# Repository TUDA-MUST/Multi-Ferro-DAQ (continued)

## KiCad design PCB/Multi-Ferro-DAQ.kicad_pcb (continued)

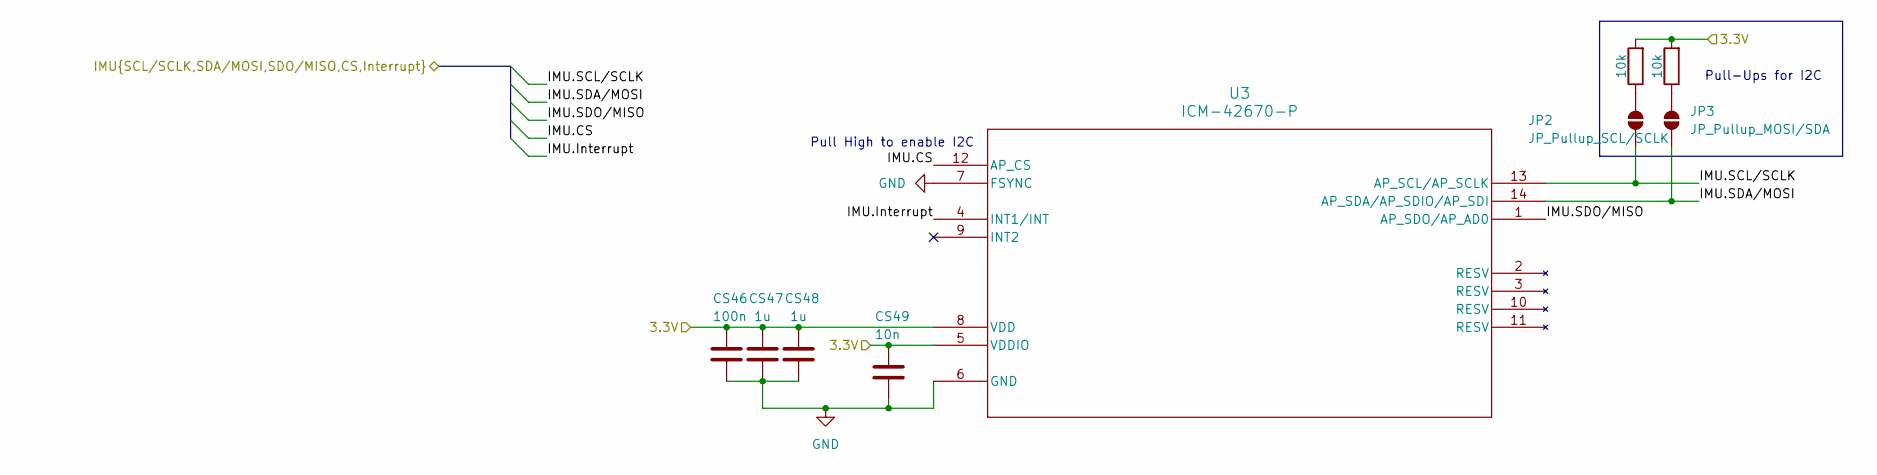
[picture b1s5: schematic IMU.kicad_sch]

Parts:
CS46: 100n; C_0603_1608Metric; LCSC C14663
CS47, CS48: 1u; C_0603_1608Metric; LCSC C15849
CS49: 10n; C_0603_1608Metric; LCSC C57112
JP2: JP_Pullup_SCL/SCLK; SolderJumper-2_P1.3mm_Open_RoundedPad1.0x1.5mm
JP3: JP_Pullup_MOSI/SDA; SolderJumper-2_P1.3mm_Open_RoundedPad1.0x1.5mm
R15, R16: 10k; R_0603_1608Metric; LCSC C25804
U3: ICM-42670-P; LGA14_2.5X3X0.76_IVS; LCSC C3288646

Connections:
/ADC/DVDD: CS46.2, CS47.1, CS48.1, CS49.2, R15.2, R16.2, U3.5 (VDDIO), U3.8 (VDD); also elsewhere on the board
/ESP32/IMU.CS: U3.12 (AP_CS); also elsewhere on the board
/ESP32/IMU.Interrupt: U3.4 (INT1/INT); also elsewhere on the board
/ESP32/IMU.SCL/SCLK: JP2.1 (A), U3.13 (AP_SCL/AP_SCLK); also elsewhere on the board
/ESP32/IMU.SDA/MOSI: JP3.1 (A), U3.14 (AP_SDA/AP_SDIO/AP_SDI); also elsewhere on the board
/ESP32/IMU.SDO/MISO: U3.1 (AP_SDO/AP_AD0); also elsewhere on the board
GND: CS46.1, CS47.2, CS48.2, CS49.1, U3.6 (GND), U3.7 (FSYNC); also elsewhere on the board
unnamed: JP2.2 (B), R15.1
unnamed: JP3.2 (B), R16.1

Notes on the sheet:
Pull-Ups for I2C
Pull High to enable I2C

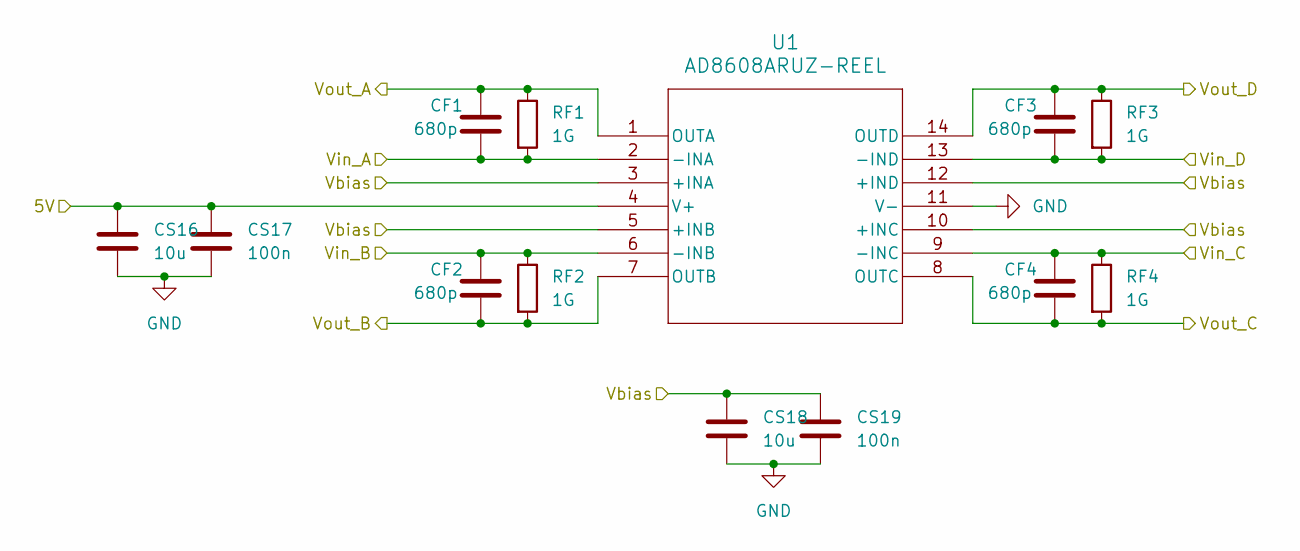
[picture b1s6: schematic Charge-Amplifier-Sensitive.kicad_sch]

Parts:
CF1, CF2, CF3, CF4: 680p; C_0805_2012Metric_Pad1.18x1.45mm_HandSolder; LCSC C1835
CS16, CS18: 10u; C_0603_1608Metric; LCSC C19702
CS17, CS19: 100n; C_0603_1608Metric; LCSC C14663
RF1, RF2, RF3, RF4: 1G; R_0805_2012Metric_Pad1.20x1.40mm_HandSolder; LCSC C2484710
U1: AD8608ARUZ-REEL; RU_14_ADI; LCSC C578777

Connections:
/ADC/AVDD: CS16.1, CS17.1, U1.4 (V+); also elsewhere on the board
/ADC/Charge-Amplifier-PORT I/Vin_A: CF1.2, RF1.2, U1.2 (-INA); also elsewhere on the board
/ADC/Charge-Amplifier-PORT I/Vin_B: CF2.1, RF2.1, U1.6 (-INB); also elsewhere on the board
/ADC/Charge-Amplifier-PORT I/Vin_C: CF4.1, RF4.1, U1.9 (-INC); also elsewhere on the board
/ADC/Charge-Amplifier-PORT I/Vin_D: CF3.2, RF3.2, U1.13 (-IND); also elsewhere on the board
/ADC/Charge-Amplifier-PORT I/Vout_A: CF1.1, RF1.1, U1.1 (OUTA); also elsewhere on the board
/ADC/Charge-Amplifier-PORT I/Vout_B: CF2.2, RF2.2, U1.7 (OUTB); also elsewhere on the board
/ADC/Charge-Amplifier-PORT I/Vout_C: CF4.2, RF4.2, U1.8 (OUTC); also elsewhere on the board
/ADC/Charge-Amplifier-PORT I/Vout_D: CF3.1, RF3.1, U1.14 (OUTD); also elsewhere on the board
/ADC/Vbias: CS18.1, CS19.1, U1.3 (+INA), U1.5 (+INB), U1.10 (+INC), U1.12 (+IND); also elsewhere on the board
GND: CS16.2, CS17.2, CS18.2, CS19.2, U1.11 (V-); also elsewhere on the board

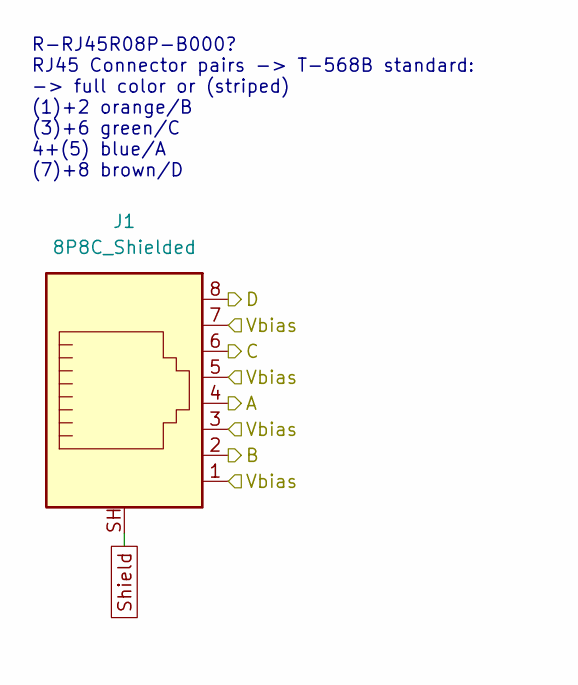
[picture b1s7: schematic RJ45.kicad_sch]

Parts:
J1: 8P8C_Shielded; R-RJ45R08P-B000; LCSC C386756

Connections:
/ADC/Charge-Amplifier-PORT I/Vin_A: J1.4; also elsewhere on the board
/ADC/Charge-Amplifier-PORT I/Vin_B: J1.2; also elsewhere on the board
/ADC/Charge-Amplifier-PORT I/Vin_C: J1.6; also elsewhere on the board
/ADC/Charge-Amplifier-PORT I/Vin_D: J1.8; also elsewhere on the board
/ADC/Vbias: J1.1, J1.3, J1.5, J1.7; also elsewhere on the board
Shield: J1.SH; also elsewhere on the board

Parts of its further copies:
J5: 8P8C_Shielded; R-RJ45R08P-B000; LCSC C386756

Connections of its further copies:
/ADC/Charge-Amplifier-PORT II/Vin_A: J5.4; also elsewhere on the board
/ADC/Charge-Amplifier-PORT II/Vin_B: J5.2; also elsewhere on the board
/ADC/Charge-Amplifier-PORT II/Vin_C: J5.6; also elsewhere on the board
/ADC/Charge-Amplifier-PORT II/Vin_D: J5.8; also elsewhere on the board
/ADC/Vbias: J5.1, J5.3, J5.5, J5.7; also elsewhere on the board
Shield: J5.SH; also elsewhere on the board

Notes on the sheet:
R-RJ45R08P-B000? RJ45 Connector pairs -> T-568B standard: -> full color or (striped) (1)+2 orange/B (3)+6 green/C 4+(5) blue/A (7)+8 brown/D

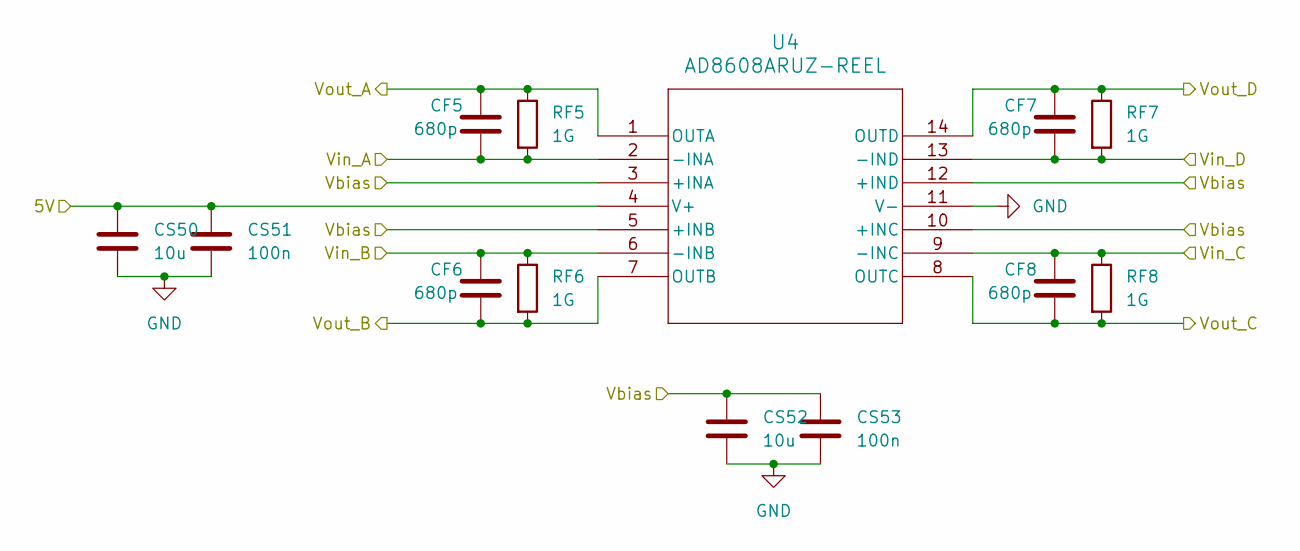
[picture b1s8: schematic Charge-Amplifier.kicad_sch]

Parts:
CF5, CF6, CF7, CF8: 680p; C_0805_2012Metric_Pad1.18x1.45mm_HandSolder; LCSC C1835
CS50, CS52: 10u; C_0603_1608Metric; LCSC C19702
CS51, CS53: 100n; C_0603_1608Metric; LCSC C14663
RF5, RF6, RF7, RF8: 1G; R_0805_2012Metric_Pad1.20x1.40mm_HandSolder; LCSC C2484710
U4: AD8608ARUZ-REEL; RU_14_ADI; LCSC C578777

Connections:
/ADC/AVDD: CS50.1, CS51.1, U4.4 (V+); also elsewhere on the board
/ADC/Charge-Amplifier-PORT II/Vin_A: CF5.2, RF5.2, U4.2 (-INA); also elsewhere on the board
/ADC/Charge-Amplifier-PORT II/Vin_B: CF6.1, RF6.1, U4.6 (-INB); also elsewhere on the board
/ADC/Charge-Amplifier-PORT II/Vin_C: CF8.1, RF8.1, U4.9 (-INC); also elsewhere on the board
/ADC/Charge-Amplifier-PORT II/Vin_D: CF7.2, RF7.2, U4.13 (-IND); also elsewhere on the board
/ADC/Charge-Amplifier-PORT II/Vout_A: CF5.1, RF5.1, U4.1 (OUTA); also elsewhere on the board
/ADC/Charge-Amplifier-PORT II/Vout_B: CF6.2, RF6.2, U4.7 (OUTB); also elsewhere on the board
/ADC/Charge-Amplifier-PORT II/Vout_C: CF8.2, RF8.2, U4.8 (OUTC); also elsewhere on the board
/ADC/Charge-Amplifier-PORT II/Vout_D: CF7.1, RF7.1, U4.14 (OUTD); also elsewhere on the board
/ADC/Vbias: CS52.1, CS53.1, U4.3 (+INA), U4.5 (+INB), U4.10 (+INC), U4.12 (+IND); also elsewhere on the board
GND: CS50.2, CS51.2, CS52.2, CS53.2, U4.11 (V-); also elsewhere on the board

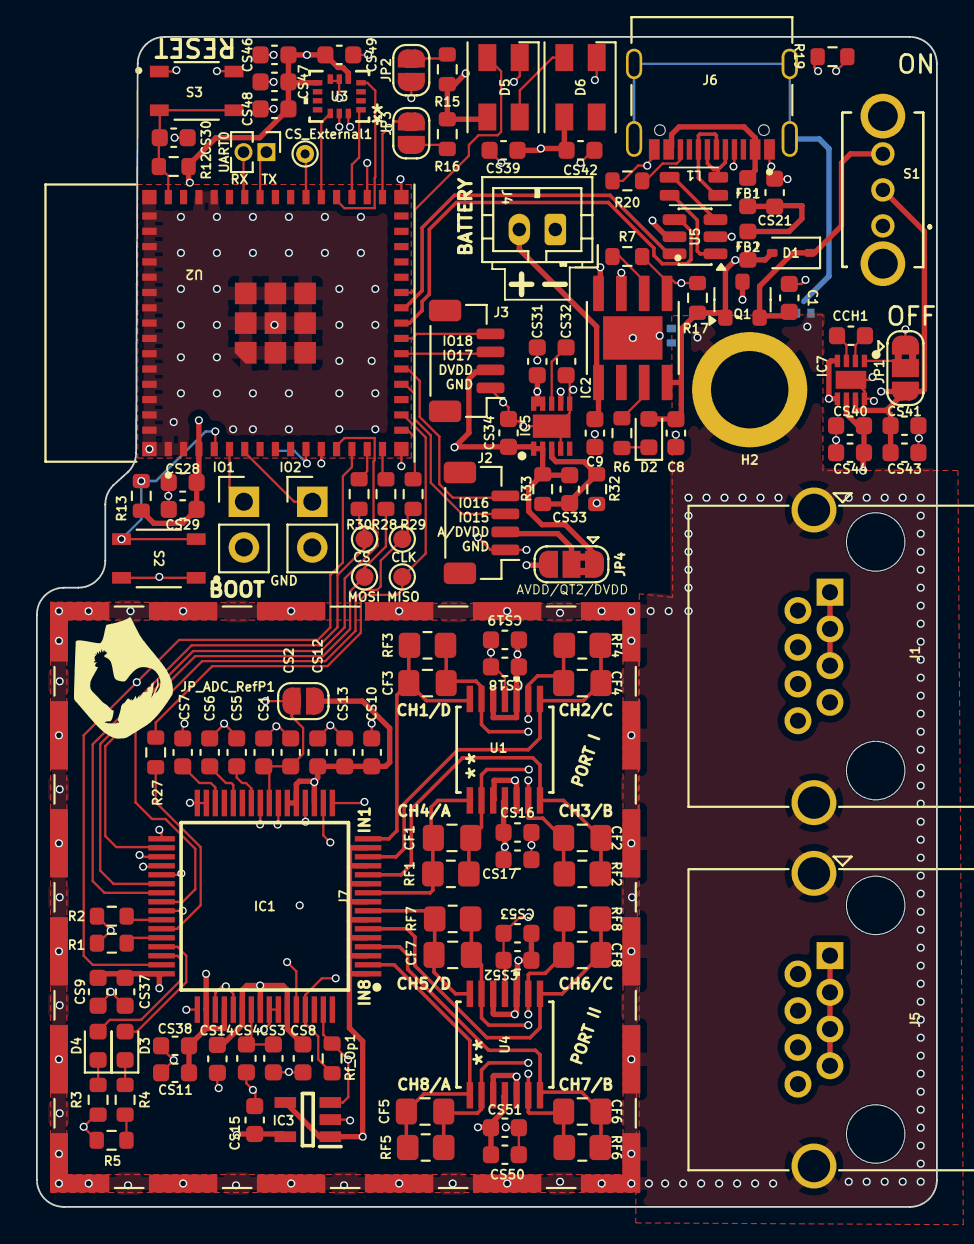
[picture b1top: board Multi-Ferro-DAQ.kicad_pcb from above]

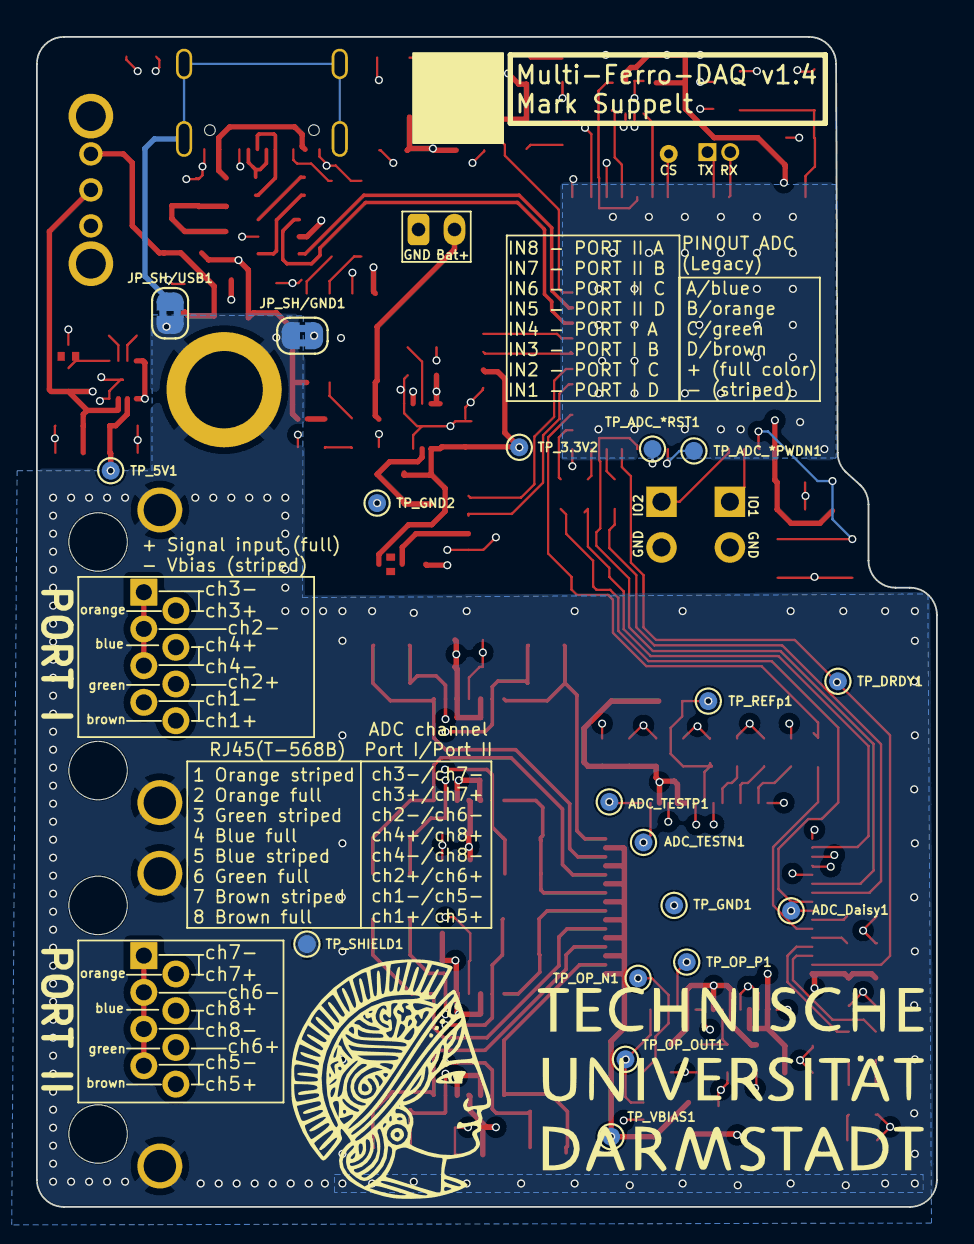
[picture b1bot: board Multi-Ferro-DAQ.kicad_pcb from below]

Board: 4 copper layers, 50.0 x 65.0 mm, 146 parts (18 on the bottom side), 95 nets.

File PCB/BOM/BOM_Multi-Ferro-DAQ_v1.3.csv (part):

Item,Qty,Designators,Value,Category,Manufacturer,MPN,Package,Specs,LCSC,Footprint,Datasheet,Notes
1,1,IC1,ADS131E08IPAGR,IC,Texas Instruments,ADS131E08IPAGR,TQFP-64,"8-ch, 24-bit simultaneous-sampling ΔΣ ADC, up to 64 kSPS, SPI",C190276,QFP50P1200X1200X120-64N,https://www.lcsc.com/datasheet/C190276.pdf,
2,1,IC2,TP4056,IC,TOP POWER ASIC,TP4056X-42-ESOP8,ESOP-8,"1-cell Li-ion linear charger, 4.2 V, ≤1 A",C2763448,SOP127P600X175-9N,https://www.lcsc.com/datasheet/C2763448.pdf,No cell protection on board – use a protected 1S Li-ion/LiPo cell.
3,1,IC3,TLV9051IDBVR,IC,Texas Instruments,TLV9051IDBVR,SOT-23-5,"RRIO op-amp, 5 MHz, 1.8–6 V",C1849429,SOT95P280X145-5N,https://www.lcsc.com/datasheet/C1849429.pdf,V_bias buffer
4,1,IC5,TPS7A9101DSKR,IC,Texas Instruments,TPS7A9101DSKR,WSON-10 2.5×2.5,"1 A adjustable low-noise LDO, 4.7 µV_RMS",C2878140,SON50P250X250X80-11N-D,https://www.lcsc.com/datasheet/C2878140.pdf,
5,1,IC7,LM2775QDSGRQ1,IC,Texas Instruments,LM2775QDSGRQ1,WSON-8 2×2,"Switched-cap boost, 5 V out, 200 mA",C2071153,SON50P200X200X80-9N,https://www.lcsc.com/datasheet/C2071153.pdf,
6,2,"U1, U4",AD8608ARUZ-REEL,IC,Analog Devices,AD8608ARUZ-REEL,TSSOP-14,"Quad CMOS RRIO op-amp, 2.7–5.5 V, 10 MHz GBW, 1 pA I_b, 75 µV V_os",C578777,RU_14_ADI,https://www.lcsc.com/datasheet/C578777.pdf,"Charge amplifiers, 2 × 4 channels"
7,1,U3,ICM-42670-P,IC,TDK InvenSense,ICM-42670-P,LGA-14 2.5×3 mm,"6-axis IMU, I²C/SPI/I3C",C3288646,LGA14_2.5X3X0.76_IVS,https://www.lcsc.com/datasheet/C3288646.pdf,Populated but not used by current firmware
8,1,U2,ESP32-S3-MINI-1-N8,Module,Espressif,ESP32-S3-MINI-1-N8,SMD module,"ESP32-S3, 8 MB flash, Wi-Fi/BLE 5, PCB antenna",C2913206,XCVR_ESP32-S3-MINI-1-N8,https://www.lcsc.com/datasheet/C2913206.pdf,
9,1,Q1,DMG2305,Transistor,TECH PUBLIC,DMG2305UX,SOT-23,"P-MOSFET, −20 V, 4.1 A, 52 mΩ @ 4.5 V",C2940629,DMG2305UX,https://www.lcsc.com/datasheet/C2940629.pdf,LCSC part is a second-source of the Diodes Inc. DMG2305UX
10,1,D1,D_Schottky,Diode,R+O,BAT60B,SOD-323,"Schottky, 10 V, 3 A, 0.6 V @ 1 A",C7502695,D_SOD-323,https://www.lcsc.com/datasheet/C7502695.pdf,
11,1,U5,WE-TVS-82400102,Diode,Würth Elektronik,82400102,SOT-23-6,"2-ch low-capacitance TVS array (WE-TVS), USB",C1975330,SOT-23-6,https://uk.farnell.com/wurth-elektronik/82400102/diode-tvs-2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,USB ESD protection
12,2,"D2, D3",LED_R,LED,Hubei KENTO,KT-0603R,0603,"Red, 615–630 nm",C2286,LED_0603_1608Metric,https://www.lcsc.com/datasheet/C2286.pdf,
13,1,D4,LED_W,LED,Hubei KENTO,KT-0603W,0603,White,C2290,LED_0603_1608Metric,https://www.lcsc.com/datasheet/C2290.pdf,"Under RF shield, flashes when ADC is configured"
14,2,"D5, D6",SK6812MINI-HS,LED,OPSCO,SK6812MINI-HS,3.5×3.5 mm,"Addressable RGB LED, 5 V",C2922787,SK6812MNI-HS,https://www.lcsc.com/datasheet/C2922787.pdf,Status LEDs
15,7,"R1, R12, R13, R15, R16, R17, R2",10k,Resistor,UNI-ROYAL,0603WAF1002T5E,0603,"10 kΩ ±1 %, 100 mW, thick film",C25804,R_0603_1608Metric,https://www.lcsc.com/datasheet/C25804.pdf,
16,2,"R19, R20",5.1k,Resistor,UNI-ROYAL,0603WAF5101T5E,0603,"5.1 kΩ ±1 %, 100 mW, thick film",C23186,R_0603_1608Metric,https://www.lcsc.com/datasheet/C23186.pdf,USB-C CC pull-downs
17,1,R27,27R,Resistor,UNI-ROYAL,0603WAF270JT5E,0603,"27 Ω ±1 %, 100 mW, thick film",C25190,R_0603_1608Metric,https://www.lcsc.com/datasheet/C25190.pdf,
18,4,"R28, R29, R30, Rf_Op1",0R,Resistor,UNI-ROYAL,0603WAF0000T5E,0603,"0 Ω jumper, 100 mW",C21189,R_0603_1608Metric,https://www.lcsc.com/datasheet/C21189.pdf,
19,3,"R3, R4, R5",100R,Resistor,UNI-ROYAL,0603WAF1000T5E,0603,"100 Ω ±1 %, 100 mW, thick film",C22775,R_0603_1608Metric,https://www.lcsc.com/datasheet/C22775.pdf,
20,1,R32,1.15k,Resistor,YAGEO,RT0603BRE071K15L,0603,"1.15 kΩ ±0.1 %, 100 mW, ±50 ppm/K, thin film",C861724,R_0603_1608Metric,https://www.lcsc.com/datasheet/C861724.pdf,LDO feedback divider (bottom). DVDD = 0.8 V × (1 + R33/R32) ≈ 3.28 V. Keep 0.1 % thin film.
21,2,"R33, R7",3.57k,Resistor,YAGEO,RT0603BRE073K57L,0603,"3.57 kΩ ±0.1 %, 100 mW, ±50 ppm/K, thin film",C326745,R_0603_1608Metric,https://www.lcsc.com/datasheet/C326745.pdf,"R33: LDO feedback divider (top), keep 0.1 % thin film. R7: TP4056 PROG resistor, I_chg ≈ 1200 V / 3.57 kΩ ≈ 336 mA (any 1 % part is fine here)."
22,1,R6,1k,Resistor,UNI-ROYAL,0603WAF1001T5E,0603,"1 kΩ ±1 %, 100 mW, thick film",C21190,R_0603_1608Metric,https://www.lcsc.com/datasheet/C21190.pdf,
23,8,"RF1, RF2, RF3, RF4, RF5, RF6, RF7, RF8",1G,Resistor,Stackpole (SEI),HVCB0805KDL1G00,0805,"1 GΩ ±10 %, 200 mW, 600 V, ±200 ppm/K, thick film",C2484710,R_0805_2012Metric_Pad1.20x1.40mm_HandSolder,https://www.lcsc.com/datasheet/C2484710.pdf,CRITICAL – charge-amp feedback resistor R_F. Sets τ = R_F·C_F = 0.68 s and the low-frequency corner; ±10 % tolerance applies directly to τ. Hand-solder footprint.
24,16,"C1, C8, C9, CS11, CS16, CS18, CS2, CS31, CS34, CS39, CS40, CS41, CS42, CS50, CS52, CS9",10u,Capacitor,Samsung Electro-Mechanics,CL10A106KP8NNNC,0603,"10 µF ±10 %, 10 V, X5R",C19702,C_0603_1608Metric,https://www.lcsc.com/datasheet/C19702.pdf,
25,11,"CCH1, CS10, CS12, CS13, CS14, CS4, CS47, CS48, CS5, CS7, CS8",1u,Capacitor,Samsung Electro-Mechanics,CL10A105KB8NNNC,0603,"1 µF ±10 %, 50 V, X5R",C15849,C_0603_1608Metric,https://www.lcsc.com/datasheet/C15849.pdf,
26,8,"CF1, CF2, CF3, CF4, CF5, CF6, CF7, CF8",680p,Capacitor,FH (Fenghua),0805CG681J500NT,0805,"680 pF ±5 %, 50 V, C0G/NP0",C1835,C_0805_2012Metric_Pad1.18x1.45mm_HandSolder,https://www.lcsc.com/datasheet/C1835.pdf,CRITICAL – charge-amp feedback capacitor C_F; sets gain ≈ 1/C_F. Must be C0G/NP0; do not substitute X7R. Hand-solder footprint.
27,14,"CS1, CS15, CS17, CS19, CS29, CS3, CS32, CS37, CS38, CS43, CS44, CS46, CS51, CS53",100n,Capacitor,YAGEO,CC0603KRX7R9BB104,0603,"100 nF ±10 %, 50 V, X7R",C14663,C_0603_1608Metric,https://www.lcsc.com/datasheet/C14663.pdf,
28,1,CS21,680n,Capacitor,CCTC,TCC0603X7R684K500CT,0603,"680 nF ±10 %, 50 V, X7R",C5360852,C_0603_1608Metric,https://www.lcsc.com/datasheet/C5360852.pdf,
29,3,"CS28, CS30, CS6",22u,Capacitor,Samsung Electro-Mechanics,CL10A226MQ8NRNC,0603,"22 µF ±20 %, 6.3 V, X5R",C59461,C_0603_1608Metric,https://www.lcsc.com/datasheet/C59461.pdf,
30,2,"CS33, CS49",10n,Capacitor,FH (Fenghua),0603B103K500NT,0603,"10 nF ±10 %, 50 V, X7R",C57112,C_0603_1608Metric,https://www.lcsc.com/datasheet/C57112.pdf,
31,2,"FB1, FB2",FerriteBead,Inductor,Würth Elektronik,742792641,0603,"Ferrite bead, 300 Ω @ 100 MHz, 2 A, 150 mΩ",C2649308,L_0603_1608Metric,https://fat.lcsc.com/product-detail/Ferrite-Beads_Wurth-Elek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,
32,1,L1,Choke_Wurth_WE-CNSW_744232090,Inductor,Würth Elektronik,744232090,1206 (WE-CNSW),"Common-mode choke, 90 Ω @ 100 MHz, 370 mA, USB 2.0",C2649327,L_CommonMode_Wurth_WE-CNSW-1206,https://www.digikey.co.uk/en/products/detail/w%C3%BCrth-elek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,USB data lines
33,2,"GPIO1, GPIO2",Conn_01x02_Pin,Connector,XFCN,PZ254V-11-02P,"THT, 2.54 mm",1×2 pin header,C492401,PinHeader_1x02_P2.54mm_Vertical,https://www.lcsc.com/datasheet/C492401.pdf,
34,2,"J1, J5",8P8C_Shielded,Connector,CKMTW,R-RJ45R08P-B000,"THT, right angle","RJ45 8P8C, shielded, no LEDs, no magnetics",C386756,R-RJ45R08P-B000,https://www.lcsc.com/datasheet/C386756.pdf,"Sensor inputs, 4 channels per port (T-568B pinout on silkscreen)"
35,2,"J2, J3",Conn_01x04_Socket,Connector,JST,BM04B-SRSS-TBT(LF)(SN),"SMD, 1.0 mm","SH 1×4 header, vertical",C495539,JST_SH_BM04B-SRSS-TB_1x04-1MP_P1.00mm_Vertical,https://www.lcsc.com/datasheet/C495539.pdf,
36,1,J4,Conn_01x02_Pin,Connector,JST,B2B-PH-K-E(LF)(SN),"THT, 2.0 mm",PH 1×2 header,C594142,JST_PH_B2B-PH-K_1x02_P2.00mm_Vertical,https://www.lcsc.com/datasheet/C594142.pdf,Battery connector
37,1,J6,TYPE-C-31-M-12,Connector,Korean Hroparts (HRO),TYPE-C-31-M-12,SMD,"USB Type-C receptacle, 16 pin",C165948,HRO_TYPE-C-31-M-12,https://www.lcsc.com/datasheet/C165948.pdf,
38,1,S1,SK-12D02-VG3,Switch,Korean Hroparts (HRO),SK-12D02-VG3,"THT, right angle",SPDT slide switch,C136723,SK12D02VG3,https://www.lcsc.com/datasheet/C136723.pdf,Power switch
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
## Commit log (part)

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2024-10-07 first
2024-10-08 added first parts
2024-10-09 finished SPI, working on ADC
2024-10-11 added missing
2024-10-17 save progress
2024-10-23 added IMU
2024-11-07 no changes
2024-11-26 added a first blink for the SchlaubiSchlumpf board
    example uses the FastLED library
2024-11-26 added datasheet for LEDs
2024-11-26 added a first example to utilize the IMU via SPI
2024-11-26 Update README.md to include calibration notice
2024-12-06 Added files for ADC test and libs
2024-12-06 Create ADC folder
2024-12-06 Added ADS131 test and libs to the correct file path
    Non working version! Header compiles, ADS131E08.cpp needs to be written.
2024-12-09 updated adc_test
    .h are and .cpp driver files are converted but have not recieved testing as of yet.
    Problems may arise @ ADS131E08_wait_drdy_int as this funciton is handled by
    interrupts on the STM32.
2024-12-10 started debugging, struggling @startup function
2024-12-12 tried to fix some bugs by reasoning with the programm
2024-12-17 made progress with debugging
    The esp32 is now runnable and reaches the loop(). Although we send data to dhe ADC
    we don't recieve any at the moment.
2024-12-17 Delete ADC/ardu_adc_test/lib/spi_multiple_buses.c
    file deprecated
2024-12-17 Delete ADC/ardu_adc_test/lib/spi_multiple_buses.h
    filed deprecated
2024-12-19 continued with now working HW (pull pwrdwn to HIGH!)
2025-01-06 Got WREG & RREG to work
2025-01-07 first fully working version, probably contains bugs
2025-01-07 Datatsheet for AD8606
2025-01-08 working software, as far as capure 8,9 are concerned
    Maybe offset can be added to readout? Why do channels inluence each other?
2025-01-15 Uploading dual-core-pointer version
2025-01-17 working dual core on 4kSPS + Serial.print()
2025-01-17 Now working @940SPS
2025-01-20 chars work @1kSPS, but crashes after 4674/4675 print cycles
2025-01-31 Begann trying to connect to Matlab via WiFi
2025-02-10 commendted out debug prints
2025-02-10 saving progress
2025-02-10 started dual core wifi-udp data readout
2025-02-10 added MATLAB scripts that are in use
2025-02-12 Working but slow version
2025-02-12 Working script for 8 raw floats per package
2025-02-12 Packaged data & start of sampling @right moment to avoid queing
2025-02-12 handles packages & autoconnect
2025-02-14 update Opamp
2025-02-17 Started working on ISR
2025-02-18 Working 4kSPS version
2025-02-18 4kSPS with timestamp in microseconds
2025-02-18 handles 4kSPS with timestamps
2025-02-20 added some timing analytics for testing
2025-03-13 Added TCP for WiFi
2025-03-13 Added TCP for Arduino
2025-03-17 moved lib to a better viewable position
2025-03-17 updated lib
2025-03-17 did minor tweaks for convinience
2025-03-17 Added a rudementary reconnect by software resetting
2025-03-17 sending sample count to esp
2025-03-19 Added labels and legend
2025-04-15 upped wait time for MATLAB to send smaple size to up stability
2025-04-15 Implemented CHAN_GAIN Settings
2025-04-15 Impelmented CHAN_GAIN Settings
2025-04-16 Out of bounds checking by setting channel to +/- 7000
2025-04-17 Added some commentary
2025-04-23 started extending via Matlab configuration
2025-04-24 More params can now be edited via Matlab
2025-04-24 Matlab can now edit more settings; started simulink model
2025-09-17 newest order 17.09
2025-10-09 added "Stop" functionality to MATLAB
2025-10-09 ESP stops measurement if WiFi.client sends anything
2025-10-09 forgot to uncomment something back in
2025-10-09 and forgot to remove the useless if...
2025-10-14 corrected cap/resistor
2025-10-29 Fixed faulty CHAN7/8 behaiviour
2025-10-29 Changed from µs to s in plots
2025-10-29 Update README.md
    First version of README
2025-10-30 Update README.md
    fixed a typo
2025-10-30 Update README.md
    formatted with help of ChatGPT
2025-10-30 Update README.md
    fixed typo
2025-10-30 Update README.md
    forgot to mention ESP32 IP Adress
2025-11-18 changed file structure
    Changed file structure and naming to clarify uses. Moved not used code to /Software/ADC_readout/deprecated/
2025-11-18 added a "Falshing" section to README.md
2025-11-18 fixed a typo
2025-11-19 added saving measurement data to .csv files in MATLAB script
2025-11-26 started migration from MATLAB
2025-11-27 first GUI skelleton
2025-11-28 resolved IP adress independent connect via UDP broadcast
2025-11-28 automated most of the connect/ disconnect
    + set up a enum for package types
2025-11-28 backup at end of day
2025-12-01 made hotspot credentials configureable on ESP32
2025-12-02 implemented preprocessor directives for LINUX/ WINDOWS
2025-12-03 brought ESP up to speed
2025-12-03 working TCP+ Live Plotting on multiple clients
2025-12-03 made Handshake for Clientname and nmbr of channels
2025-12-04 Implemented Windows Version
2025-12-05 Working Windows version
2025-12-05 impelmented timestamp sync logic and header export
2025-12-10 fixed time issue, refactored, introduced sync_client
2025-12-11 compiled app.exe
2025-12-11 fixed race condition on SyncClient
2025-12-12 Refactored giant GUI.c into three smaler files
2025-12-15 Sending NULL-Byte as ACK upon connection
    Windows doesn't detect clients reliably without that....
2025-12-17 Working json version
    GUI on setup not correct
    GUI on load json settings not correct
2025-12-18 fully working json config/ handshake
2025-12-18 updated SyncClient to new Json Format
2025-12-19 improved UI, build safeguards for user input
2025-12-19 extended timout on connection for WINDOWS
2025-12-19 did a coarse slimming of /share/ of ~10000 files
2025-12-19 implemented small changes requested by Mark
2026-01-05 last commit before reordering into new project
2026-01-05 moved MMM into own project
2026-01-06 renamed directory
2026-01-06 Added MMM part to readme
2026-01-06 Stemma etc.
2026-01-19 corrected settings parsing on client side
2026-01-19 moved MMM_migration
2026-03-10 added channel names to MMM JSON
2026-03-14 Added Missing Components in Export
    Issue was caused by the JLCPCB Plugin which does not export components with a name longer than 7 letters
2026-03-17 renamed image folder to "doc"
2026-03-17 Revise README for ADC WiFi readout and MMM usage
    Updated references to MATLAB script and MMM firmware.
2026-03-30 added a continous MMM Client for MMMv1.2.0 onward
